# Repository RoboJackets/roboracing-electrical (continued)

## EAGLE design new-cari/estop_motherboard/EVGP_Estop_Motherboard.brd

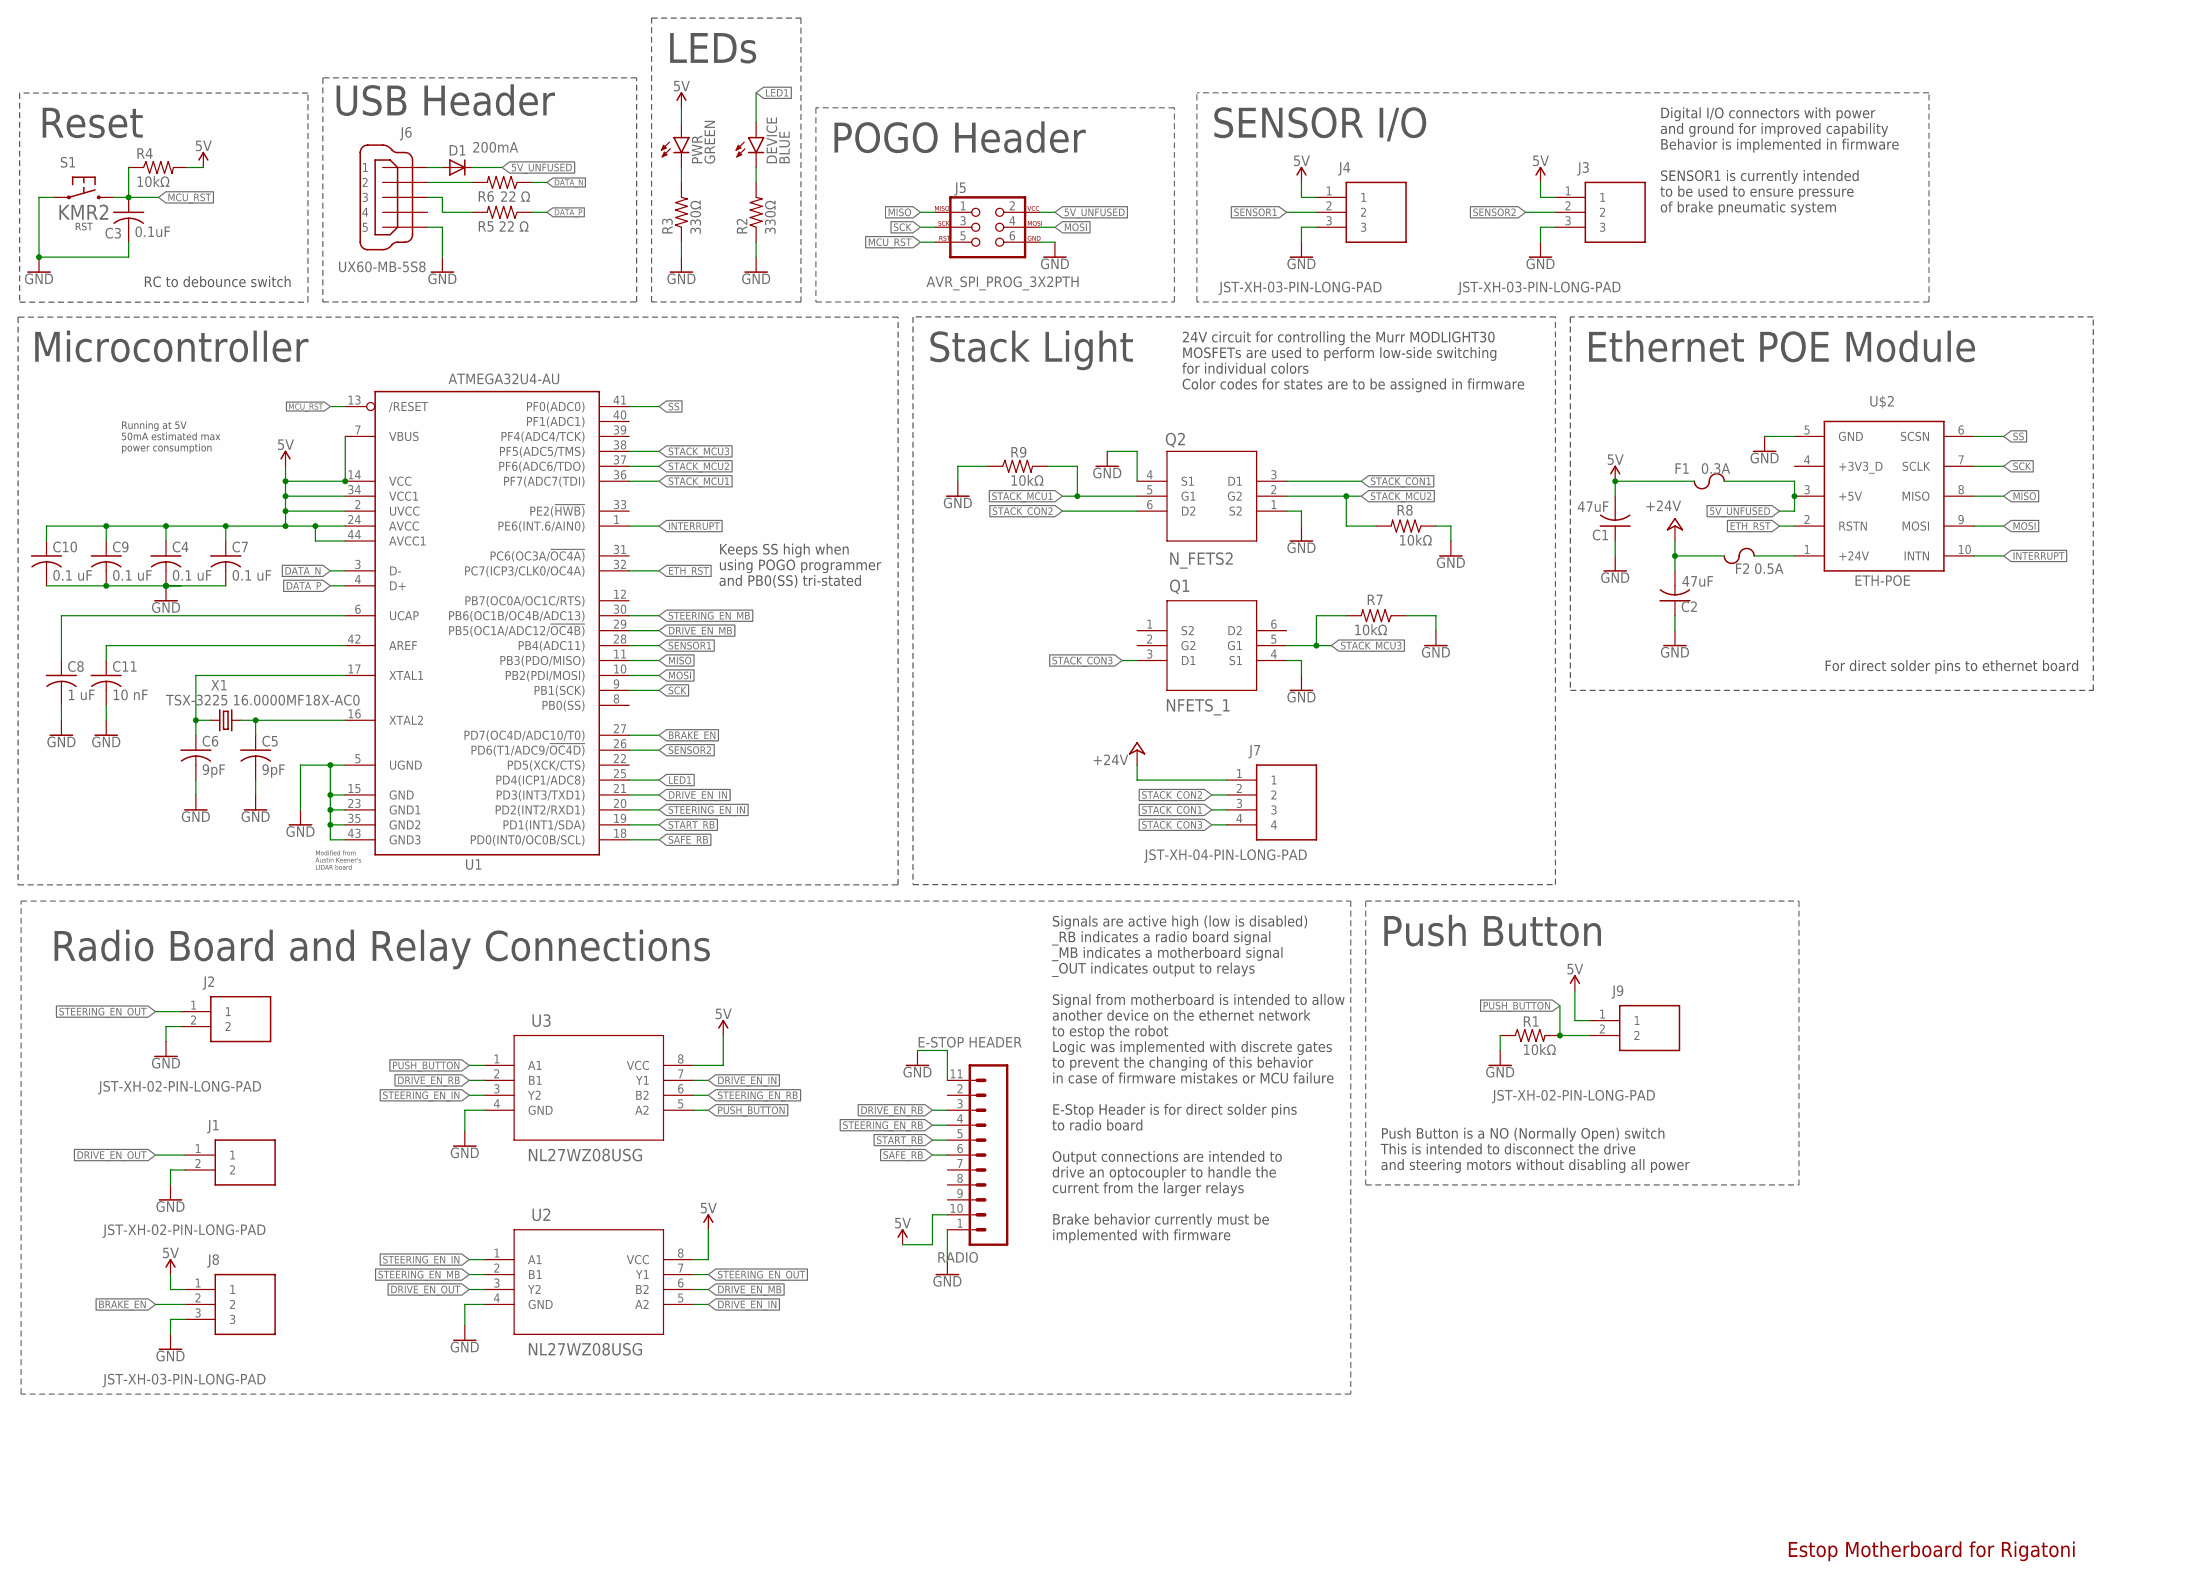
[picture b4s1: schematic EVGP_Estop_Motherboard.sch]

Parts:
C1, C2: 47uF; C1206
C3: 0.1uF; C0603
C4, C7, C9, C10: 0.1 uF; C0603
C5, C6: 9pF; C0603
C8: 1 uF; C0603
C11: 10 nF; C0603
D1: 200mA; SOD323-R
DEVICE: BLUE; CHIP-LED0603
F1: 0.3A; F1206
F2: 0.5A; F1206
J1, J2, J9: JST-XH-02-PIN-LONG-PAD; JST-XH-02-PACKAGE-LONG-PAD
J3, J4, J8: JST-XH-03-PIN-LONG-PAD; JST-XH-03-PACKAGE-LONG-PAD
J5: AVR_SPI_PROG_3X2PTH; 2X3
J6: UX60-MB-5S8
J7: JST-XH-04-PIN-LONG-PAD; JST-XH-04-PACKAGE-LONG-PAD
PWR: GREEN; CHIP-LED0603
Q1: NFETS_1; SOT-363
Q2: N_FETS2; SOT-363
R1, R4, R7, R8, R9: 10kΩ; R0603
R2, R3: 330Ω; R0603
R5, R6: 22 Ω; R0603
RADIO: E-STOP HEADER; RADIO_V1.3
S1: KMR2
U1: ATMEGA32U4-AU; TQFP44
U2, U3: NL27WZ08USG; US8_2P40X2P10
U$2: ETH-POE; HDRVR10W64P4000X254_2X5_1016X508X254B
X1: TSX-3225 16.0000MF18X-AC0; XTAL-3.2X2.5

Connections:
5V: C1.2, C4.1, C7.1, C9.1, C10.1, F1.1, J3.1, J4.1, J8.1, J9.1, PWR.A, R4.2, RADIO.10 (5V), U1.2 (UVCC), U1.7 (VBUS), U1.14 (VCC), U1.24 (AVCC), U1.34 (VCC1), U1.44 (AVCC1), U2.8 (VCC), U3.8 (VCC)
5V_UNFUSED: D1.C, F1.2, J5.2, U$2.3 (+5V)
24V_UNFUSED: F2.2, U$2.1 (+24V)
+24V: C2.2, F2.1, J7.1
AREF: C11.1, U1.42 (AREF)
BRAKE_EN: J8.2, U1.27 (PD7(OC4D/ADC10/T0))
DATA_N: R6.1, U1.3 (D-)
DATA_P: R5.1, U1.4 (D+)
DRIVE_EN_IN: U1.21 (PD3(INT3/TXD1)), U2.5 (A2), U3.7 (Y1)
DRIVE_EN_MB: U1.29 (PB5(OC1A/ADC12/!OC4B)), U2.6 (B2)
DRIVE_EN_OUT: J1.1, U2.3 (Y2)
DRIVE_EN_RB: RADIO.3 (D1), U3.2 (B1)
ETH_RST: U1.32 (PC7(ICP3/CLK0/OC4A)), U$2.2 (RSTN)
GND: C1.1, C2.1, C3.2, C4.2, C5.2, C6.2, C7.2, C8.2, C9.2, C10.2, C11.2, J1.2, J2.2, J3.3, J4.3, J5.6, J6.5, J8.3, Q1.4 (S1), Q2.1 (S2), Q2.4 (S1), R1.1, R2.1, R3.1, R7.1, R8.1, R9.1, RADIO.1 (GND), RADIO.11 (GND), S1.1.1 (1), S1.1.2 (1), U1.5 (UGND), U1.15 (GND), U1.23 (GND1), U1.35 (GND2), U1.43 (GND3), U2.4 (GND), U3.4 (GND), U$2.5 (GND)
INTERRUPT: U1.1 (PE6(INT.6/AIN0)), U$2.10 (INTN)
LED1: DEVICE.A, U1.25 (PD4(ICP1/ADC8))
MCU_RST: C3.1, J5.5, R4.1, S1.2.1 (2), S1.2.2 (2), U1.13 (/RESET)
MISO: J5.1, U1.11 (PB3(PDO/MISO)), U$2.8 (MISO)
MOSI: J5.4, U1.10 (PB2(PDI/MOSI)), U$2.9 (MOSI)
unnamed: PWR.C, R3.2
unnamed: J6.2, R6.2
unnamed: DEVICE.C, R2.2
unnamed: D1.A, J6.1
unnamed: J6.3, R5.2
PUSH_BUTTON: J9.2, R1.2, U3.1 (A1), U3.5 (A2)
SAFE_RB: RADIO.6 (D4), U1.18 (PD0(INT0/OC0B/SCL))
SCK: J5.3, U1.9 (PB1(SCK)), U$2.7 (SCLK)
SENSOR1: J4.2, U1.28 (PB4(ADC11))
SENSOR2: J3.2, U1.26 (PD6(T1/ADC9/!OC4D))
SS: U1.41 (PF0(ADC0)), U$2.6 (SCSN)
STACK_CON1: J7.3, Q2.3 (D1)
STACK_CON2: J7.2, Q2.6 (D2)
STACK_CON3: J7.4, Q1.3 (D1)
STACK_MCU1: Q2.5 (G1), R9.2, U1.36 (PF7(ADC7(TDI))
STACK_MCU2: Q2.2 (G2), R8.2, U1.37 (PF6(ADC6/TDO))
STACK_MCU3: Q1.5 (G1), R7.2, U1.38 (PF5(ADC5/TMS))
START_RB: RADIO.5 (D3), U1.19 (PD1(INT1/SDA))
STEERING_EN_IN: U1.20 (PD2(INT2/RXD1)), U2.1 (A1), U3.3 (Y2)
STEERING_EN_MB: U1.30 (PB6(OC1B/OC4B/ADC13)), U2.2 (B1)
STEERING_EN_OUT: J2.1, U2.7 (Y1)
STEERING_EN_RB: RADIO.4 (D2), U3.6 (B2)
UCAP: C8.1, U1.6 (UCAP)
XTAL1: C6.1, U1.17 (XTAL1), X1.1
XTAL2: C5.1, U1.16 (XTAL2), X1.3 (2)

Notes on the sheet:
Modified from Austin Keener's LIDAR board
POGO Header
RC to debounce switch
Reset
LEDs
Running at 5V 50mA estimated max power consumption
Microcontroller
USB Header
Keeps SS high when using POGO programmer and PB0(SS) tri-stated
Radio Board and Relay Connections
SENSOR I/O
Stack Light
Ethernet POE Module
Estop Motherboard for Rigatoni
Push Button
Signals are active high (low is disabled) _RB indicates a radio board signal _MB indicates a motherboard signal _OUT indicates output to relays Signal from motherboard is intended to allow another device on the ethernet network to estop the robot Logic was implemented with discrete gates to prevent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
Push Button is a NO (Normally Open) switch This is intended to disconnect the drive and steering motors without disabling all power
24V circuit for controlling the Murr MODLIGHT30 MOSFETs are used to perform low-side switching for individual colors Color codes for states are to be assigned in firmware
Digital I/O connectors with power and ground for improved capability Behavior is implemented in firmware SENSOR1 is currently intended to be used to ensure pressure of brake pneumatic system
For direct solder pins to ethernet board

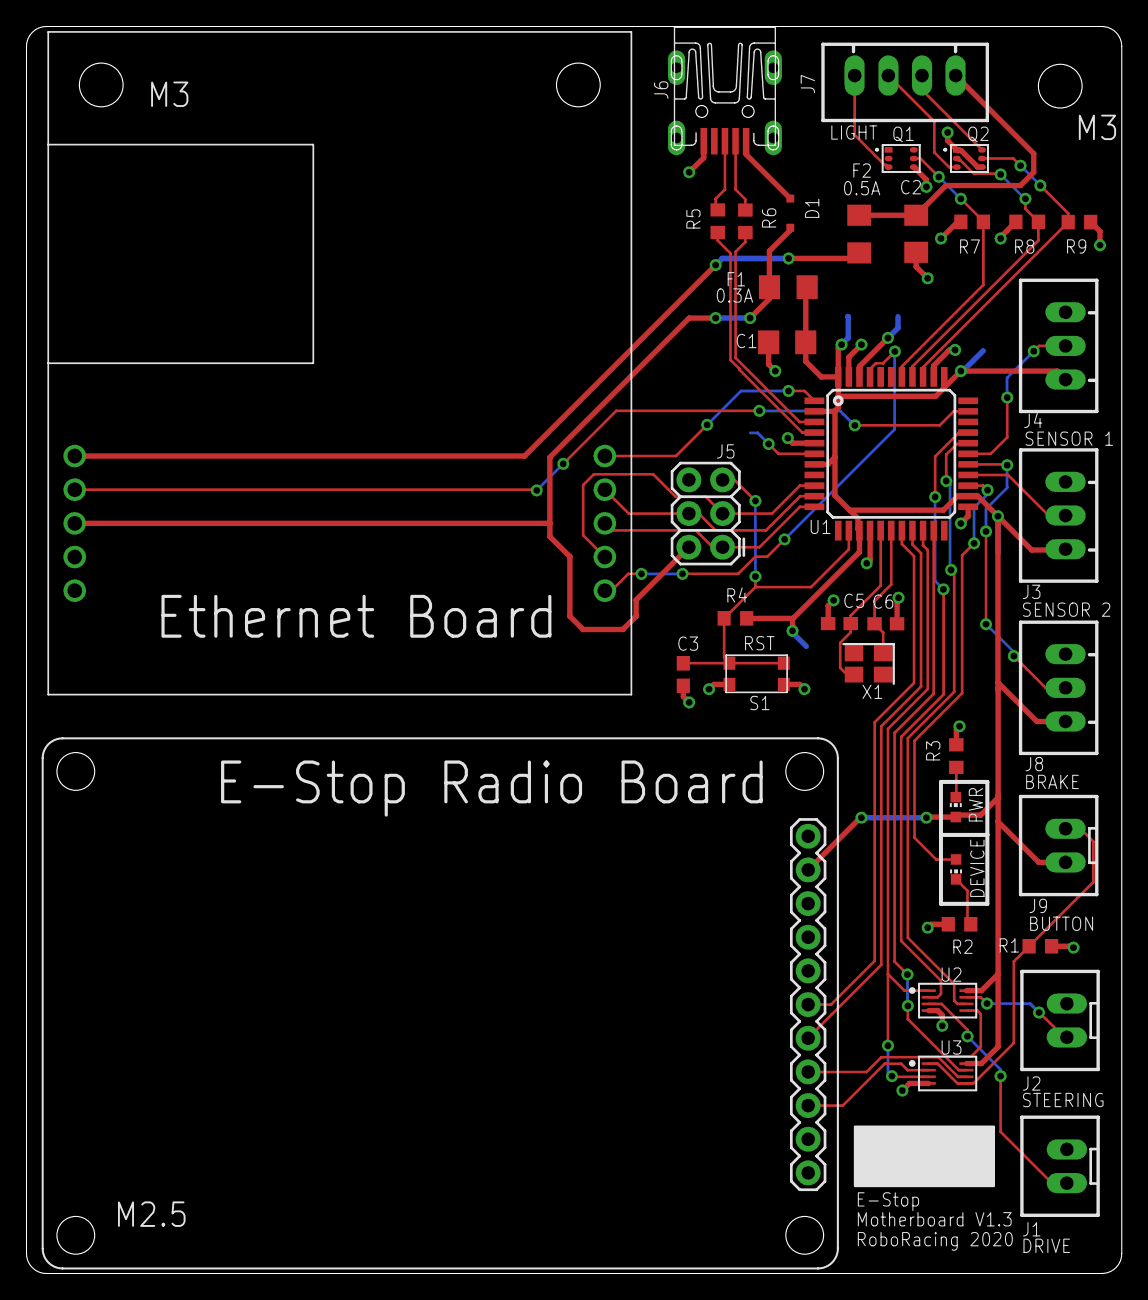
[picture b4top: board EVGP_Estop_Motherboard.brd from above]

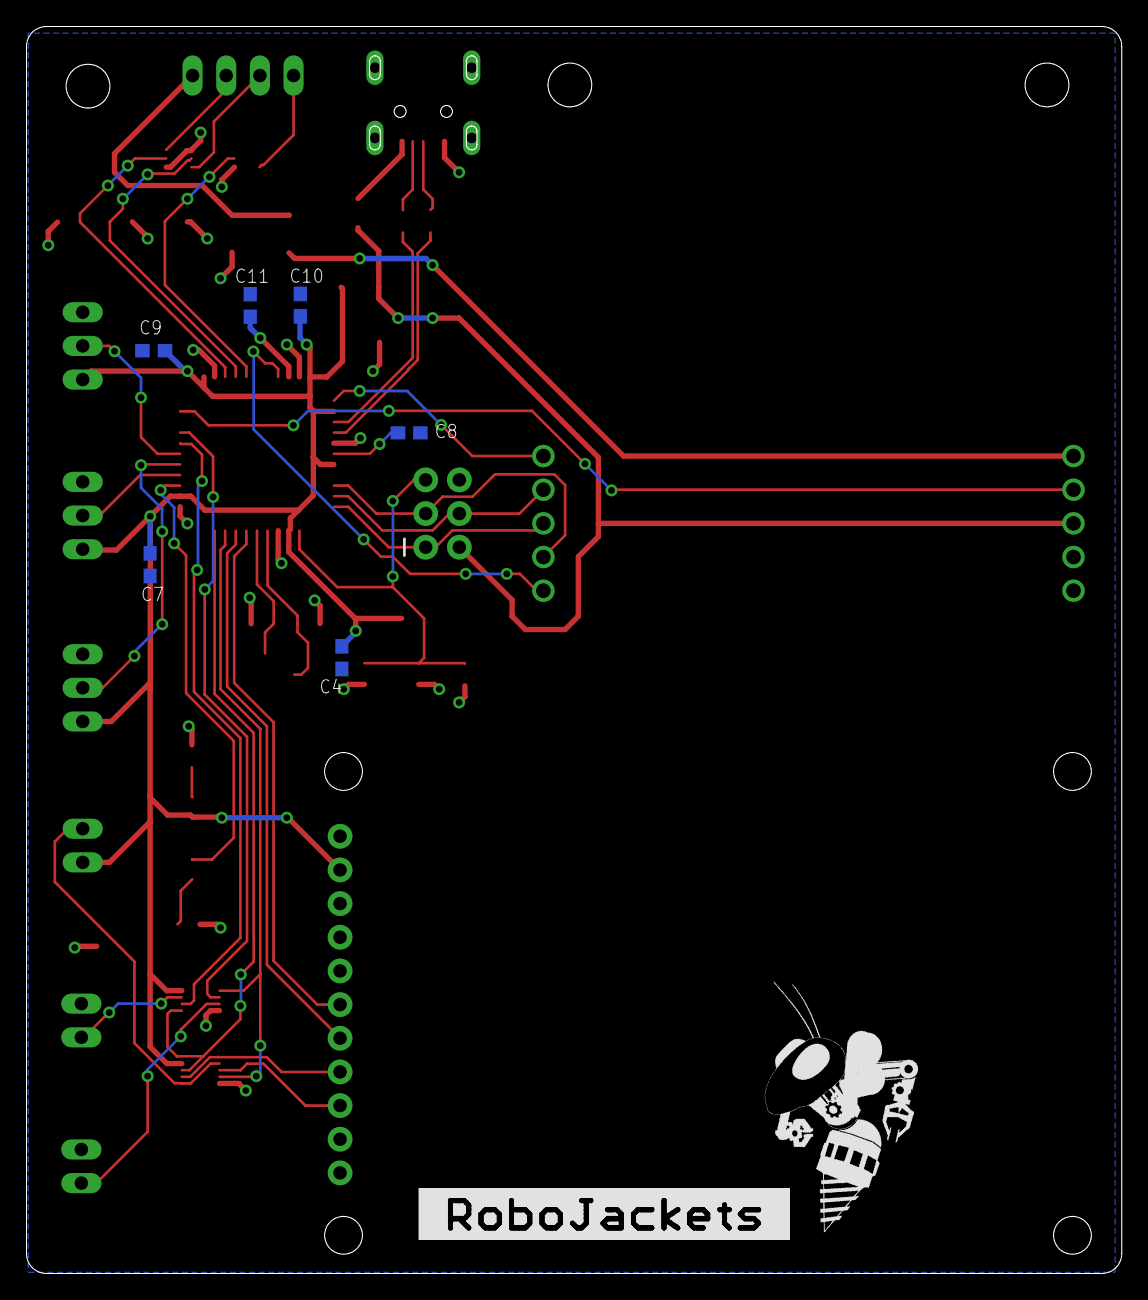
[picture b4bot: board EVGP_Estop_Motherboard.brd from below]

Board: 2 copper layers, 82.6 x 94.1 mm, 45 parts (8 on the bottom side), 44 nets.

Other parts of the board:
U$1: ROBOBUZZ_1.0X
U$3: ROBOJACKETS

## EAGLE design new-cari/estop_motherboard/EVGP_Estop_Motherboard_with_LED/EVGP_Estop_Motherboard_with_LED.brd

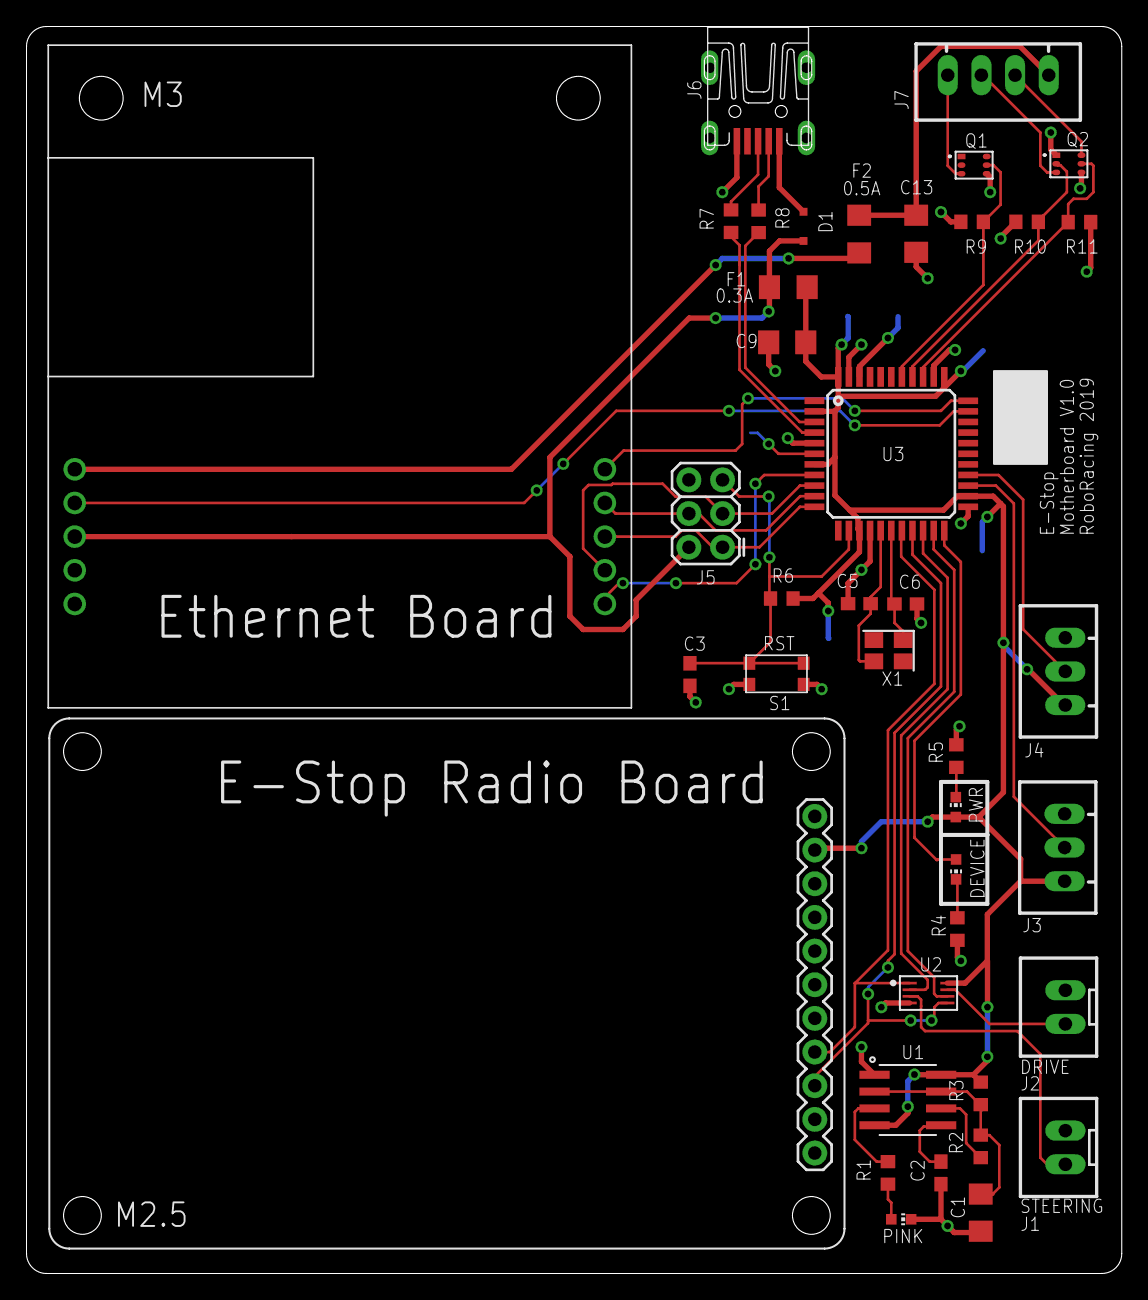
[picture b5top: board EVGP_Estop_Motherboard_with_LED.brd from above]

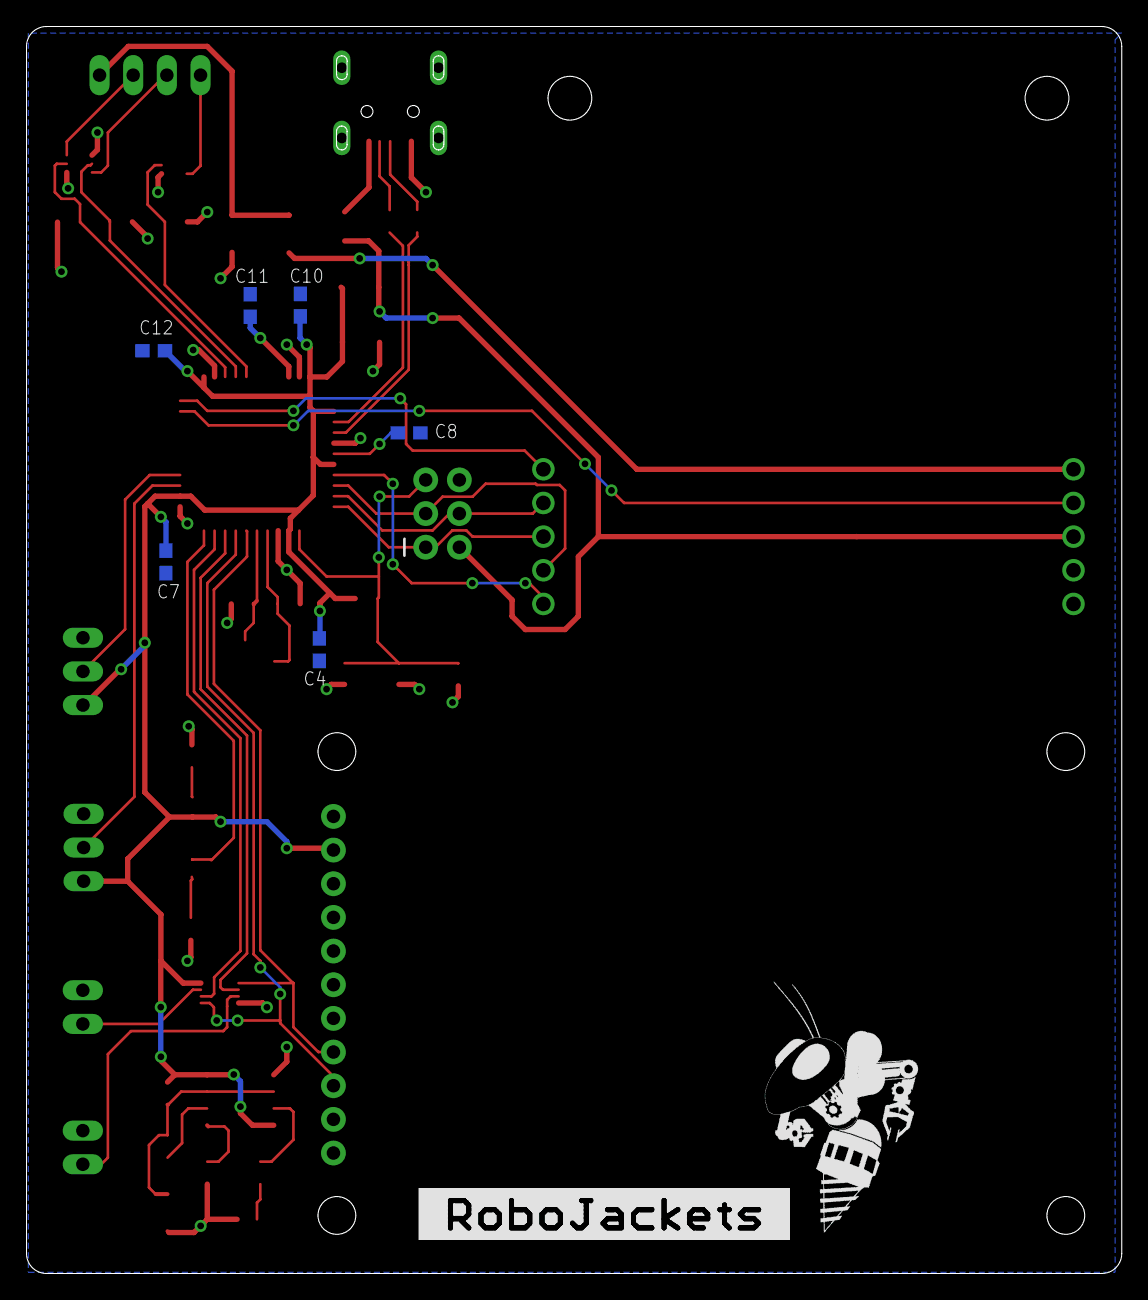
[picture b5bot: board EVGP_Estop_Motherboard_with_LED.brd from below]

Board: 2 copper layers, 82.6 x 94.1 mm, 48 parts (8 on the bottom side), 43 nets.

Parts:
C1: 1uF; C1206
C2: 0.01uF; C0603
C3: 0.1uF; C0603
C4, C7, C10, C12: 0.1 uF; C0603
C5, C6: 9pF; C0603
C8: 1 uF; C0603
C9, C13: 47uF; C1206
C11: 10 nF; C0603
D1: 200mA; SOD323-R
DEVICE: BLUE; CHIP-LED0603
F1: 0.3A; F1206
F2: 0.5A; F1206
J1: STEERING; JST-XH-02-PACKAGE-LONG-PAD
J2: DRIVE; JST-XH-02-PACKAGE-LONG-PAD
J3, J4: JST-XH-03-PIN-LONG-PAD; JST-XH-03-PACKAGE-LONG-PAD
J5: AVR_SPI_PROG_3X2PTH; 2X3
J6: UX60-MB-5S8
J7: JST-XH-04-PACKAGE-LONG-PAD
LED3: PINK; CHIP-LED0603
PWR: GREEN; CHIP-LED0603
Q1: N_FET2; SOT-363
Q2: N_FET1; SOT-363
R1: 220Ω; R0603
R2: 100kΩ; R0603
R3: 1kΩ; R0603
R4, R5: 330Ω; R0603
R6: 10k; R0603
R7, R8: 22 Ω; R0603
R9, R10, R11: 10kΩ; R0603
RADIO: E-STOP HEADER; RADIO_V1.3
S1: KMR2
U1: LM555CMX/NOPBM08A-M; M08A-M
U2: NL27WZ08USG; US8_2P40X2P10
U3: ATMEGA32U4-AU; TQFP44
U$1: ROBOBUZZ_1.0X
U$2: ETH-POE; HDRVR10W64P4000X254_2X5_1016X508X254B
U$3: ROBOJACKETS
X1: TSX-3225 16.0000MF18X-AC0; XTAL-3.2X2.5

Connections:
5V: C4.1, C7.1, C9.2, C10.1, C12.1, F1.1, J3.1, J4.1, PWR.A, R3.2, R6.2, RADIO.10, U1.4, U1.8, U2.8, U3.2, U3.7, U3.14, U3.24, U3.34, U3.44
5V_UNFUSED: D1.C, F1.2, J5.2, U$2.3
24V_UNFUSED: F2.2, U$2.1
+24V: C13.2, F2.1, J7.1
AREF: C11.1, U3.42
DATA_N: R8.1, U3.3
DATA_P: R7.1, U3.4
DRIVE_EN: J2.1, U2.7
DRIVE_EN_DB: U2.6, U3.21
DRIVE_EN_RB: RADIO.3, U2.5, U3.19
ETH_RST: U3.32, U$2.2
GND: C1.2, C2.2, C3.2, C4.2, C5.2, C6.2, C7.2, C8.2, C9.1, C10.2, C11.2, C12.2, C13.1, J1.2, J2.2, J3.3, J4.3, J5.6, J6.5, LED3.C, Q1.4, Q2.1, Q2.4, R4.1, R5.1, R9.1, R10.1, R11.1, RADIO.1, RADIO.11, S1.1.1, S1.1.2, U1.1, U2.4, U3.5, U3.15, U3.23, U3.35, U3.43, U$2.5
INTERRUPT: U3.33, U$2.10
LED1: DEVICE.A, U3.22
MCU_RST: C3.1, J5.5, R6.1, S1.2.1, S1.2.2, U3.13
MISO: J5.1, U3.11, U$2.8
MOSI: J5.4, U3.10, U$2.9
unnamed: LED3.A, R1.1
unnamed: R2.2, U1.6
unnamed: PWR.C, R5.2
unnamed: C2.1, U1.5
unnamed: J6.2, R8.2
unnamed: DEVICE.C, R4.2
unnamed: D1.A, J6.1
unnamed: R1.2, U1.3
unnamed: J6.3, R7.2
SCK: J5.3, U3.9, U$2.7
SENSOR1: J4.2, U3.26
SENSOR2: J3.2, U3.25
SS: U3.8, U$2.6
STACK_CON1: J7.2, Q2.6
STACK_CON2: J7.3, Q2.3
STACK_CON3: J7.4, Q1.3
STACK_MCU1: Q2.5, R11.2, U3.36
STACK_MCU2: Q2.2, R10.2, U3.37
STACK_MCU3: Q1.5, R9.2, U3.38
STEERING_EN: J1.1, U2.3
STEERING_EN_DB: U2.2, U3.20
STEERING_EN_RB: RADIO.4, U2.1, U3.18
TRIG: C1.1, R2.1, R3.1, U1.2, U1.7
UCAP: C8.1, U3.6
XTAL1: C6.1, U3.17, X1.1
XTAL2: C5.1, U3.16, X1.3

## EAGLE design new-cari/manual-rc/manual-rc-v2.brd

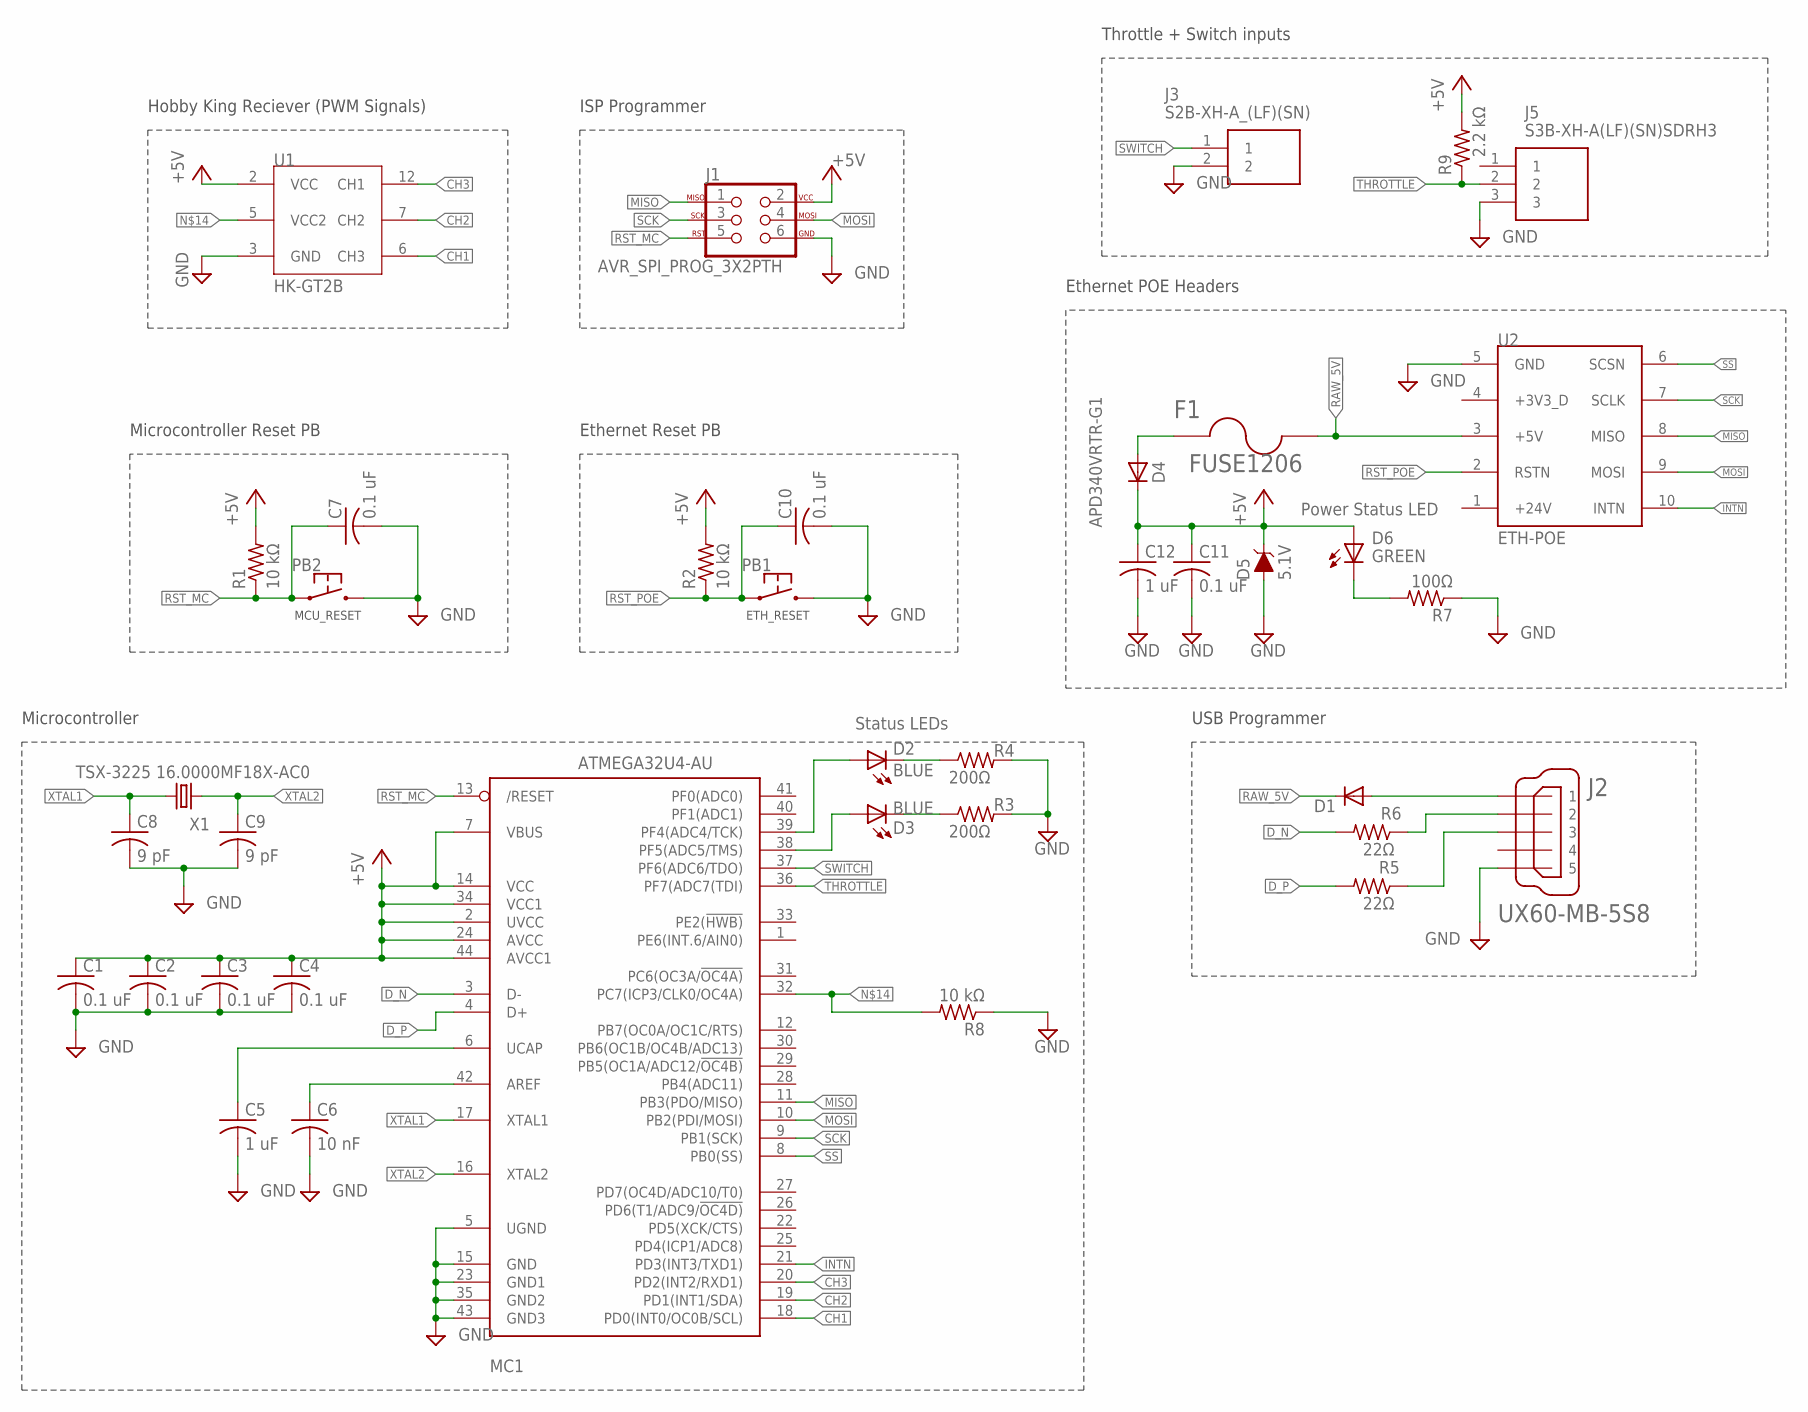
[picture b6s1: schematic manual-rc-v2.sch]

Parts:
C1, C2, C3, C4, C7, C10, C11: 0.1 uF; C0603
C5, C12: 1 uF; C0603
C6: 10 nF; C0603
C8, C9: 9 pF; C0603
D1: DIODESOD; SOD-323
D2, D3: BLUE; CHIP-LED0603
D4: APD340VRTR-G1; DO-214AC
D5: 5.1V; SOD-323
D6: GREEN; CHIP-LED0603
F1: FUSE1206; F1206
J1: AVR_SPI_PROG_3X2PTH; 2X3
J2: UX60-MB-5S8
J3: S2B-XH-A_(LF)(SN); SHDR2W80P0X250_1X2_740X1150X61
J5: S3B-XH-A(LF)(SN)SDRH3; SHDR4
MC1: ATMEGA32U4-AU; TQFP44
PB1, PB2: PTS645
R1, R2, R8: 10 kΩ; R0603
R3, R4: 200Ω; R0603W
R5, R6: 22Ω; R0603
R7: 100Ω; R0603W
R9: 2.2 kΩ; R0603
U1: HK-GT2B; HDRVR12W64P254_4X3_1016X508X254B
U2: ETH-POE; HDRVR10W64P4000X254_2X5_1016X508X254B
X1: TSX-3225 16.0000MF18X-AC0; XTAL-3.2X2.5

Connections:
+5V: C1.1, C2.1, C3.1, C4.1, C11.1, C12.1, D4.C, D5.C, D6.A, J1.2, MC1.2 (UVCC), MC1.7 (VBUS), MC1.14 (VCC), MC1.24 (AVCC), MC1.34 (VCC1), MC1.44 (AVCC1), R1.2, R2.2, R9.2, U1.2 (VCC)
CH1: MC1.18 (PD0(INT0/OC0B/SCL)), U1.6 (CH3)
CH2: MC1.19 (PD1(INT1/SDA)), U1.7 (CH2)
CH3: MC1.20 (PD2(INT2/RXD1)), U1.12 (CH1)
D_N: MC1.3 (D-), R6.2
D_P: MC1.4 (D+), R5.2
GND: C1.2, C2.2, C3.2, C4.2, C5.2, C6.2, C7.2, C8.2, C9.2, C10.2, C11.2, C12.2, D5.A, J1.6, J2.5, J3.2, J5.3, MC1.5 (UGND), MC1.15 (GND), MC1.23 (GND1), MC1.35 (GND2), MC1.43 (GND3), PB1.P$3 (2), PB1.P$4 (2), PB2.P$3 (2), PB2.P$4 (2), R3.2 (PIN2), R4.2 (PIN2), R7.1 (PIN1), R8.1, U1.3 (GND), U2.5 (GND)
INTN: MC1.21 (PD3(INT3/TXD1)), U2.10 (INTN)
MISO: J1.1, MC1.11 (PB3(PDO/MISO)), U2.8 (MISO)
MOSI: J1.4, MC1.10 (PB2(PDI/MOSI)), U2.9 (MOSI)
unnamed: C5.1, MC1.6 (UCAP)
unnamed: C6.1, MC1.42 (AREF)
unnamed: D2.A, MC1.39 (PF4(ADC4/TCK))
unnamed: D3.C (K), R3.1 (PIN1)
unnamed: J2.2, R6.1
unnamed: D1.2 (A), J2.1
unnamed: J2.3, R5.1
unnamed: D6.C (K), R7.2 (PIN2)
unnamed: D2.C (K), R4.1 (PIN1)
unnamed: D4.A, F1.1
unnamed: D3.A, MC1.38 (PF5(ADC5/TMS))
unnamed: MC1.32 (PC7(ICP3/CLK0/OC4A)), R8.2, U1.5 (VCC2)
RAW_5V: D1.1 (C), F1.2, U2.3 (+5V)
RST_MC: C7.1, J1.5, MC1.13 (/RESET), PB2.P$1 (1), PB2.P$2 (1), R1.1
RST_POE: C10.1, PB1.P$1 (1), PB1.P$2 (1), R2.1, U2.2 (RSTN)
SCK: J1.3, MC1.9 (PB1(SCK)), U2.7 (SCLK)
SS: MC1.8 (PB0(SS)), U2.6 (SCSN)
SWITCH: J3.1, MC1.37 (PF6(ADC6/TDO))
THROTTLE: J5.2, MC1.36 (PF7(ADC7(TDI)), R9.1
XTAL1: C8.1, MC1.17 (XTAL1), X1.1
XTAL2: C9.1, MC1.16 (XTAL2), X1.3 (2)

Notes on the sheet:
Hobby King Reciever (PWM Signals)
Microcontroller
ISP Programmer
Ethernet Reset PB
Microcontroller Reset PB
Ethernet POE Headers
USB Programmer
Power Status LED
Status LEDs
BLUE
Throttle + Switch inputs

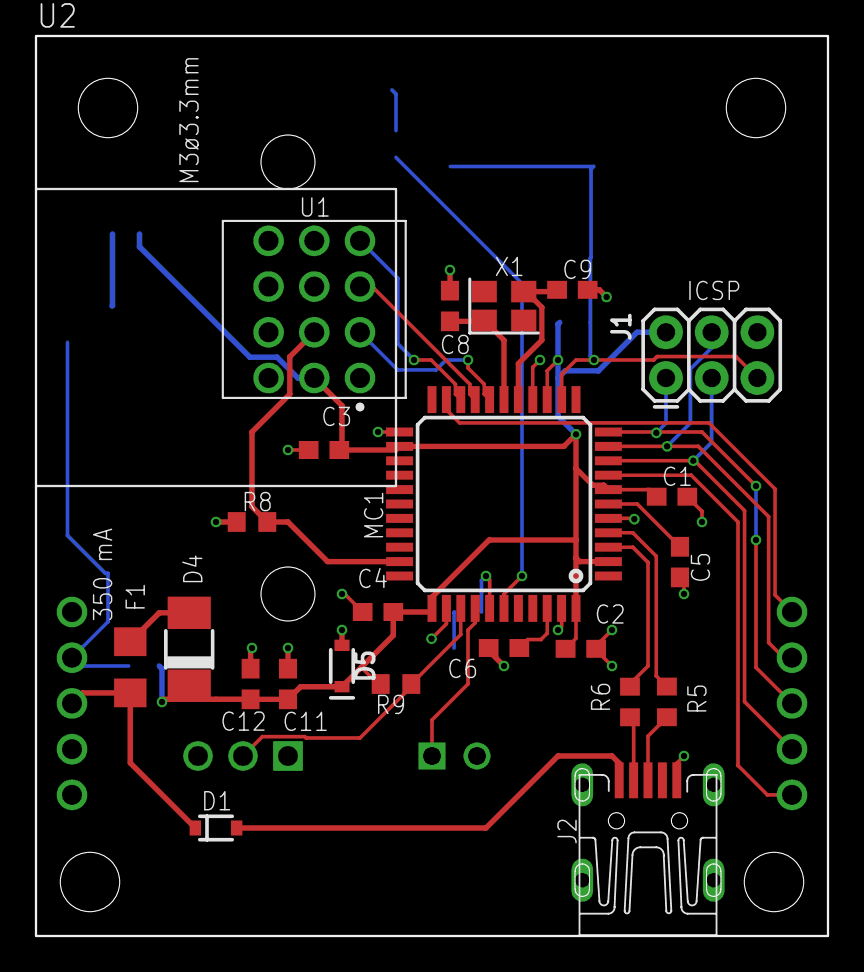
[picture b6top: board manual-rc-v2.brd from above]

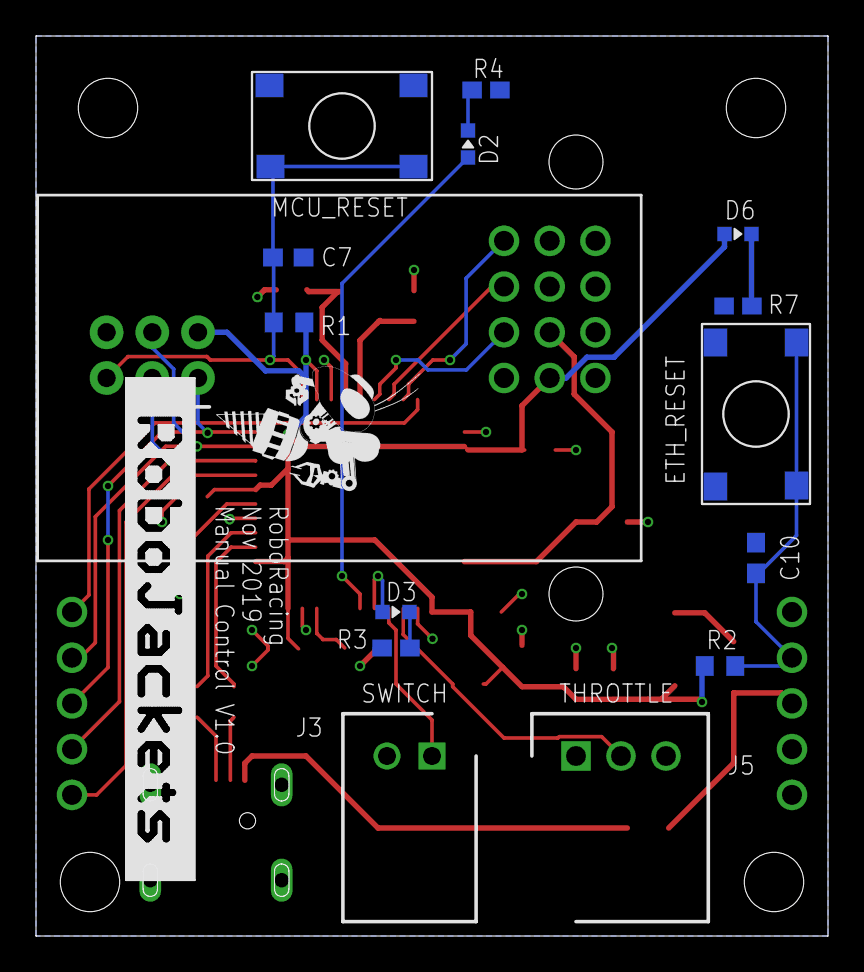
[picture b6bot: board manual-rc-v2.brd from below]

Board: 2 copper layers, 44.0 x 50.0 mm, 40 parts (16 on the bottom side), 31 nets.

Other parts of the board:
U$3: ROBOBUZZ_0.6X
U$4: ROBOJACKETS

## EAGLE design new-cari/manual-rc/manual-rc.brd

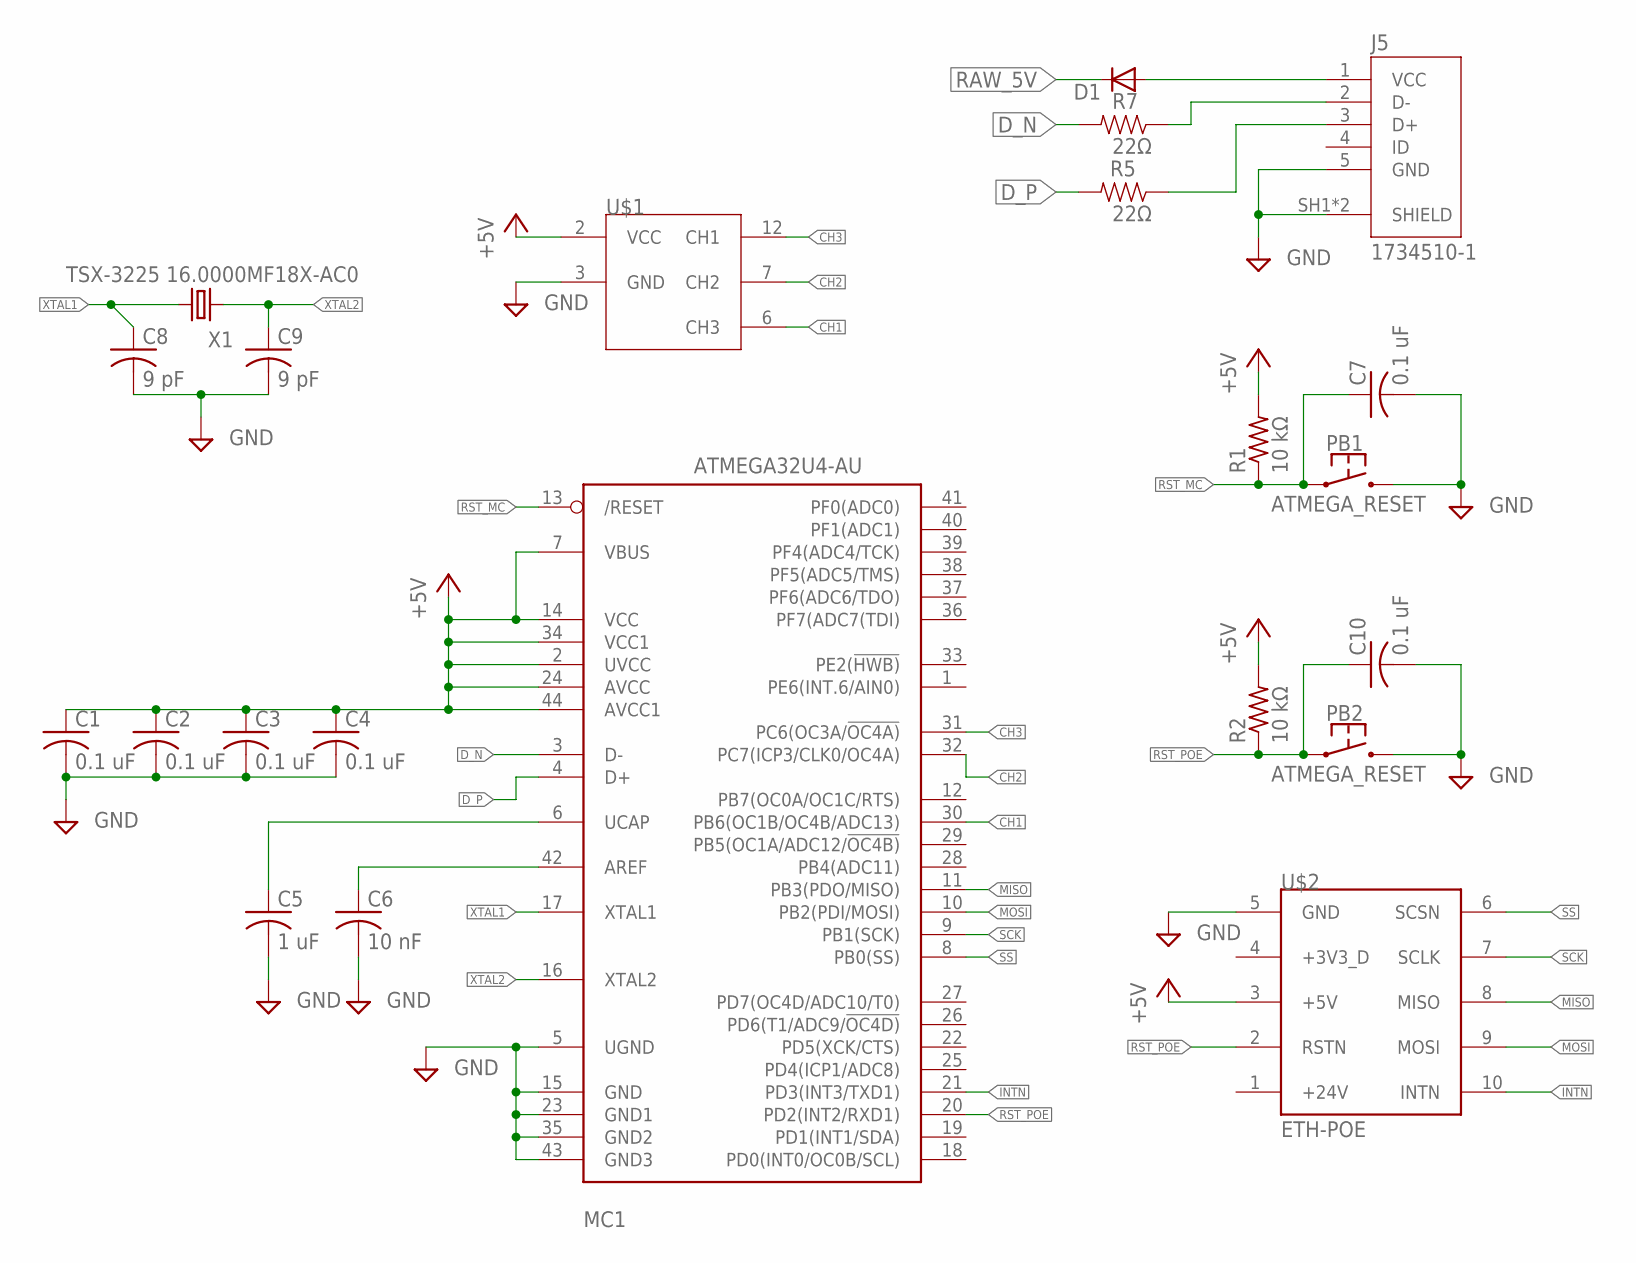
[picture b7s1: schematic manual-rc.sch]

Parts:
C1, C2, C3, C4, C7, C10: 0.1 uF; C0603
C5: 1 uF; C0603
C6: 10 nF; C0603
C8, C9: 9 pF; C0603
D1: DIODESOD; SOD-323
J5: 1734510-1; TE_1734510-1
MC1: ATMEGA32U4-AU; TQFP44
PB1, PB2: ATMEGA_RESET; TACT_PB_RA
R1, R2: 10 kΩ; R0603
R5, R7: 22Ω; 0603-RES
U$1: HK-GT2B; HDRVR12W64P254_4X3_1016X508X254B
U$2: ETH-POE; HDRVR10W64P4000X254_2X5_1016X508X254B
X1: TSX-3225 16.0000MF18X-AC0; XTAL-3.2X2.5

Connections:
+5V: C1.1, C2.1, C3.1, C4.1, MC1.2 (UVCC), MC1.7 (VBUS), MC1.14 (VCC), MC1.24 (AVCC), MC1.34 (VCC1), MC1.44 (AVCC1), U$1.2 (VCC), U$2.3 (+5V)
CH1: MC1.30 (PB6(OC1B/OC4B/ADC13)), U$1.6 (CH3)
CH2: MC1.32 (PC7(ICP3/CLK0/OC4A)), U$1.7 (CH2)
CH3: MC1.31 (PC6(OC3A/!OC4A)), U$1.12 (CH1)
D2_N: J5.2 (D-), R7.1
D2_P: J5.3 (D+), R5.1
D_N: MC1.3 (D-), R7.2
D_P: MC1.4 (D+), R5.2
GND: C1.2, C2.2, C3.2, C4.2, C5.2, C6.2, C7.2, C10.2, PB1.P$2 (2), PB2.P$2 (2), U$1.3 (GND), U$2.5 (GND)
INTN: MC1.21 (PD3(INT3/TXD1)), U$2.10 (INTN)
MISO: MC1.11 (PB3(PDO/MISO)), U$2.8 (MISO)
MOSI: MC1.10 (PB2(PDI/MOSI)), U$2.9 (MOSI)
unnamed: C5.1, MC1.6 (UCAP)
unnamed: C6.1, MC1.42 (AREF)
unnamed: MC1.5 (UGND), MC1.15 (GND), MC1.23 (GND1), MC1.35 (GND2), MC1.43 (GND3)
unnamed: R1.2, R2.2
unnamed: J5.5 (GND), J5.SH1 (SHIELD), J5.SH2 (SHIELD)
unnamed: C8.2, C9.2
unnamed: D1.2 (A), J5.1 (VCC)
RAW_5V: D1.1 (C)
RST_MC: C7.1, MC1.13 (/RESET), PB1.P$1 (1), R1.1
RST_POE: C10.1, MC1.20 (PD2(INT2/RXD1)), PB2.P$1 (1), R2.1, U$2.2 (RSTN)
SCK: MC1.9 (PB1(SCK)), U$2.7 (SCLK)
SS: MC1.8 (PB0(SS)), U$2.6 (SCSN)
XTAL1: C8.1, MC1.17 (XTAL1), X1.1
XTAL2: C9.1, MC1.16 (XTAL2), X1.3 (2)
